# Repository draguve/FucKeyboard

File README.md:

# The FucKeyboard
This project was inspired by the following meme the rest is pretty self explanatory

## Schematic

## PCB

The repository contains the kicad project files of the FucKeyboard

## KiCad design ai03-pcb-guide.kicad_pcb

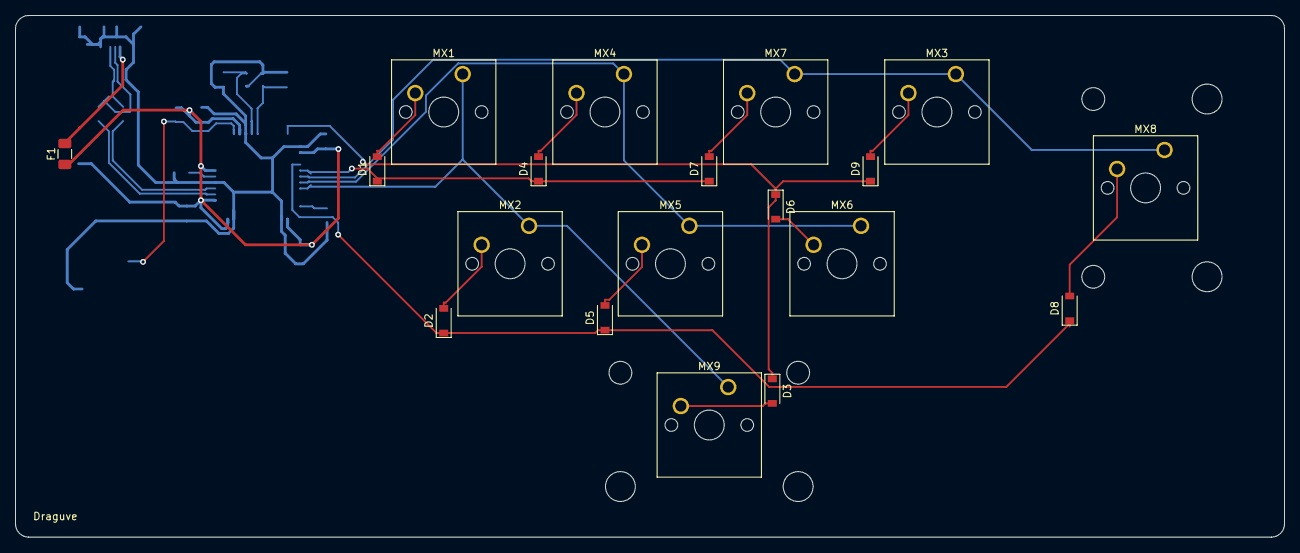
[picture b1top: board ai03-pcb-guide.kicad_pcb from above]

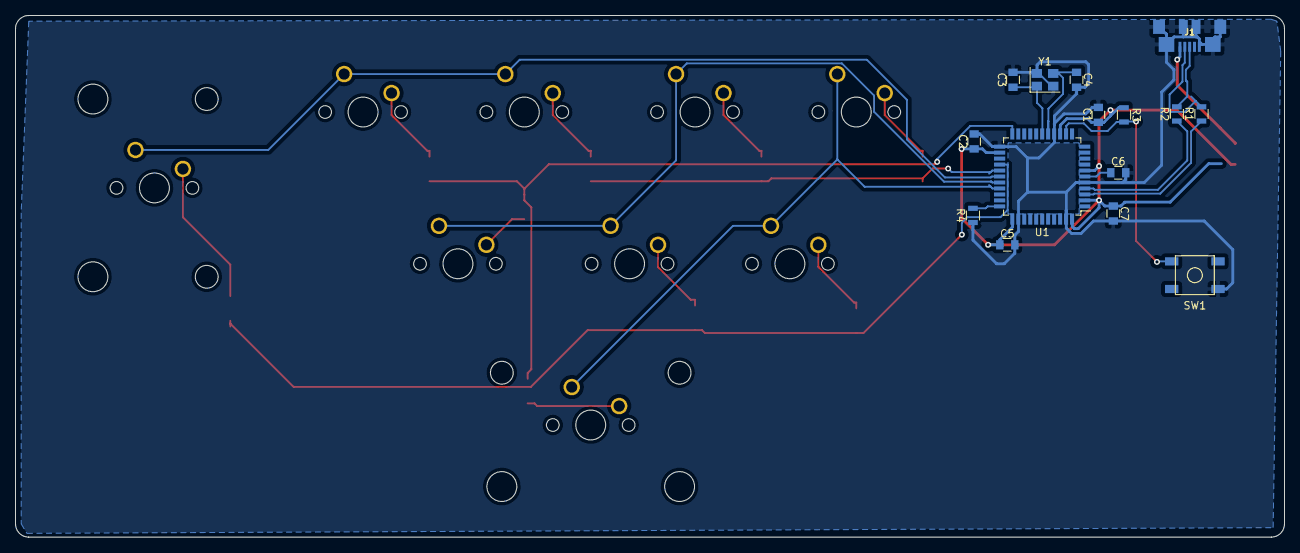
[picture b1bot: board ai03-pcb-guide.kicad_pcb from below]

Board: 2 copper layers, 169.9 x 69.8 mm, 34 parts (15 on the bottom side), 27 nets.

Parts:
C1, C2, C5: 0.1uF; C_0805
C3, C4: 22pF; C_0805
C6: 1uF; C_0805
C7: 10uF; C_0805
D1, D2, D3, D4, D5, D6, D7, D8, D9: D_Small-Device; D_SOD-123
F1: 500mA; Fuse_1206_3216Metric
J1: USB_mini_micro_B; USB_microB
MX1, MX2, MX3, MX4, MX5, MX6, MX7: MX-NoLED-MX_Alps_Hybrid; SW_Cherry_MX_1.00u_PCB
MX8: MX-NoLED-MX_Alps_Hybrid; SW_Cherry_MX_ISOEnter_PCB
MX9: MX-NoLED-MX_Alps_Hybrid; SW_Cherry_MX_2.75u_PCB
R1, R2: 22; R_0805
R3, R4: 10k; R_0805
SW1: SW_Push; SKQG-1155865
U1: ATmega32U4-AU; TQFP-44_10x10mm_Pitch0.8mm
Y1: Crystal_GND24_Small; Crystal_SMD_3225-4pin_3.2x2.5mm

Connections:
+5V: C1.1, C2.1, C5.1, C7.1, F1.1, R3.1, U1.2, U1.7, U1.14, U1.24, U1.34, U1.44
COL0: MX1.1, MX2.1, MX9.1, U1.30
COL1: MX4.1, MX5.1, MX6.1, U1.29
COL2: MX3.1, MX7.1, MX8.1, U1.28
D+: J1.3, R2.2
D-: J1.2, R1.2
GND: C1.2, C2.2, C3.2, C4.2, C5.2, C6.2, C7.2, J1.5, J1.6, R4.1, SW1.1, U1.5, U1.15, U1.23, U1.35, U1.43, Y1.2, Y1.4
unnamed: C3.1, U1.17, Y1.1
unnamed: C4.1, U1.16, Y1.3
unnamed: C6.1, U1.6
unnamed: D1.2, MX1.2
unnamed: D2.2, MX2.2
unnamed: D3.2, MX9.2
unnamed: D4.2, MX4.2
unnamed: D5.2, MX5.2
unnamed: D6.2, MX6.2
unnamed: D7.2, MX7.2
unnamed: D8.2, MX8.2
unnamed: D9.2, MX3.2
unnamed: R1.1, U1.3
unnamed: R2.1, U1.4
unnamed: R3.2, SW1.2, U1.13
unnamed: R4.2, U1.33
ROW0: D1.1, D4.1, D7.1, U1.27
ROW1: D2.1, D5.1, D8.1, U1.26
ROW2: D3.1, D6.1, D9.1, U1.22
VCC: F1.2, J1.1

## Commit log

2020-12-30 init
2020-12-30 Fixed image
2021-01-03 using pro micro instead,added tht diodes,firmware
2021-01-03 Fixed stuff
